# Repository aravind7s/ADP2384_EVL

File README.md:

# ADP2384_EVL

Hardware design files for a **12 V → 3.3 V @ 4 A** DC-DC buck converter based on the **Analog Devices ADP2384** designed using KiCad.

---

## 🧭 Overview

This project contains the complete design package — schematic, layout, and simulation files — for a compact, high-efficiency step-down converter using the ADP2384 synchronous buck regulator.  

---

## ⚙️ Board Specifications

| Parameter | Specification |
|------------|---------------|
| Input Voltage | 12 V |
| Output Voltage | 3.3 V |
| Output Current | Up to 4 A |
| Regulator IC | ADP2384 |
| Board Dimensions | 35 mm × 40 mm |
| PCB Layers | 2 layers |
| Assembly | Single-sided |

---

*3D render of the ADP2384_EVL board (35 × 40 mm)*

*Front Side*

*Back Side*

---

## 📂 Repository Structure
/

├── Board_Files/ # Schematics, BOM, PCB layout and Gerbers

├── Simulation_Files/ # LTspice file

├── TechRef/ # Datasheets and application notes

├── images/ # Renders, photos, documentation images

├── LICENSE

└── README.md

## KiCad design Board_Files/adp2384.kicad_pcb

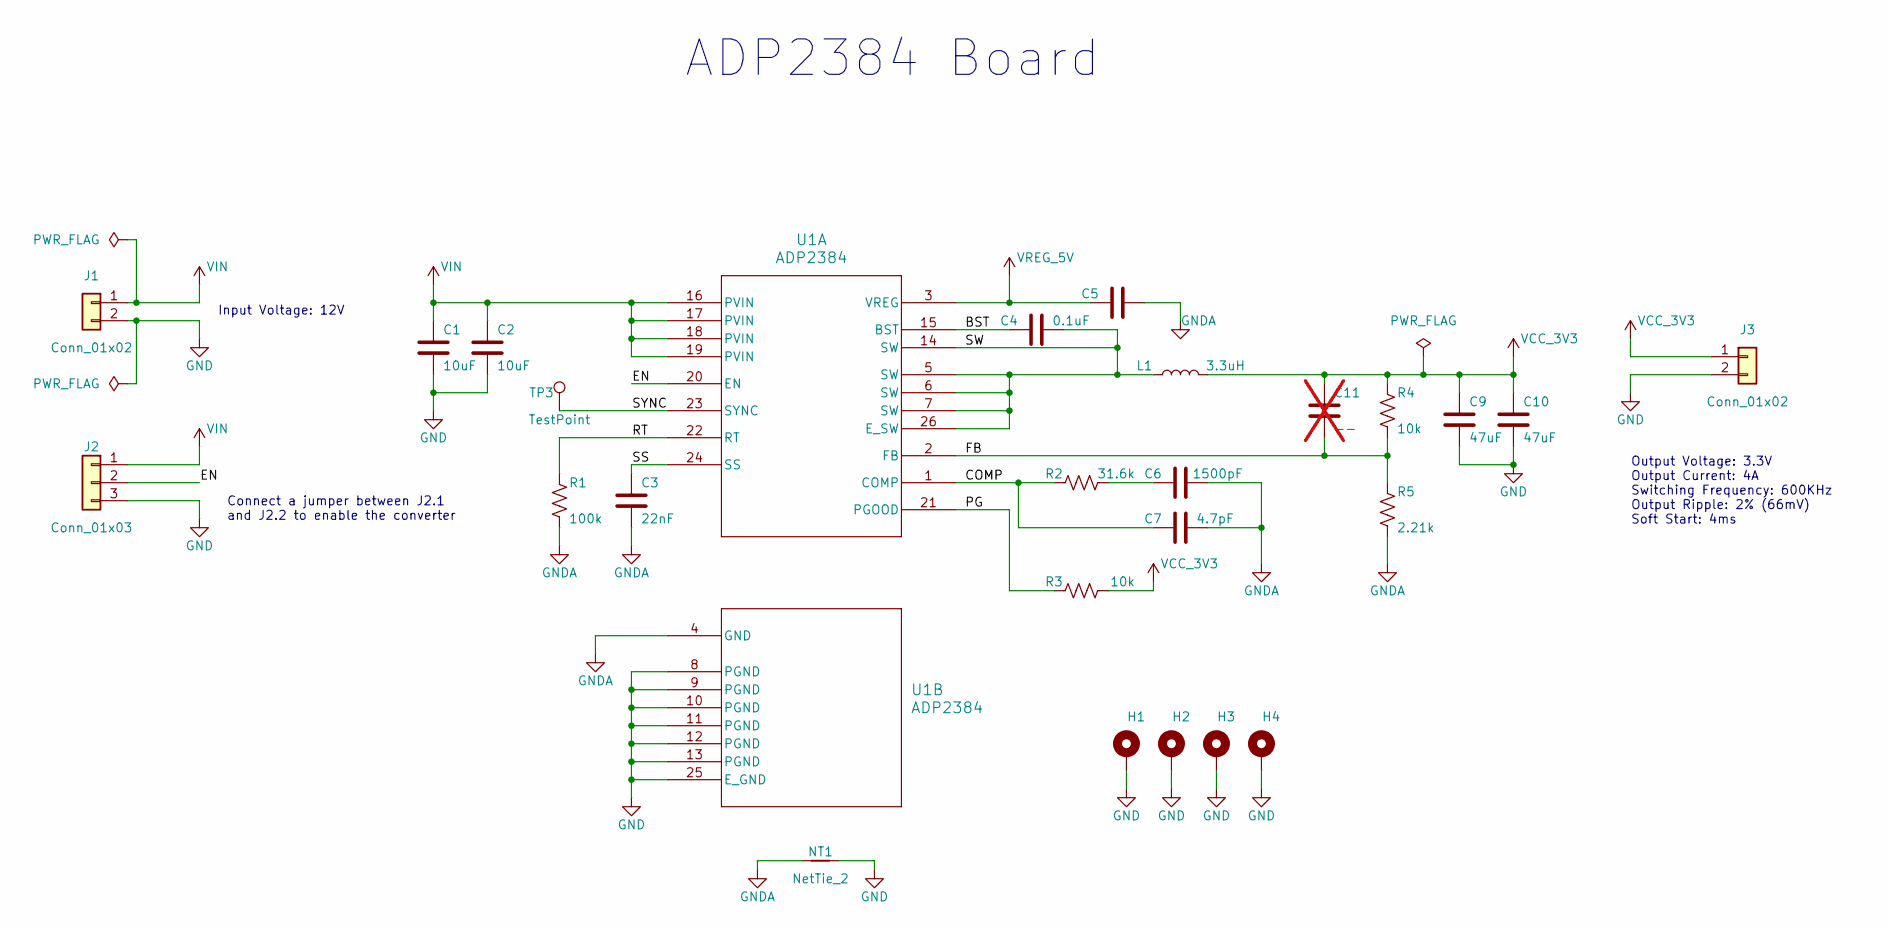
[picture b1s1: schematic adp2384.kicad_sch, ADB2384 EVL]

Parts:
C1, C2: 10uF; C_1206_3216Metric; Mfg Part No CL31B106KAHNNNE
C3: 22nF; C_0603_1608Metric; Mfg Part No GCM188R72A223KA37J
C4: 0.1uF; C_0603_1608Metric; Mfg Part No CC0603KRX7R9BB104
C5: 1uF; C_0603_1608Metric; Mfg Part No CL10B105KO8NNNC
C6: 1500pF; C_0603_1608Metric; Mfg Part No GRM1885C1H152JA01D
C7: 4.7pF; C_0603_1608Metric; Mfg Part No CC0603CPNPO9BN4R7
C9, C10: 47uF; C_1206_3216Metric; Mfg Part No GRM31CR61A476ME15L
C11: --; C_0603_1608Metric; Mfg Part No NA; not fitted
H1, H2, H3, H4: MountingHole_Pad; MountingHole_3.2mm_M3_DIN965_Pad_TopBottom; Mfg Part No NA
J1, J3: Conn_01x02; PinHeader_1x02_P2.54mm_Vertical; Mfg Part No PH1-02-UA
J2: Conn_01x03; PinHeader_1x03_P2.54mm_Vertical; Mfg Part No PH1-03-UA
L1: 3.3uH; IND_IHLP-4040DZ_VIS; Mfg Part No IHLP4040DZER3R3M01
NT1: NetTie_2; NetTie-2_THT_Pad0.3mm; Mfg Part No NA
R1: 100k; R_0603_1608Metric; Mfg Part No CRCW0603100KFKEA
R2: 31.6k; R_0603_1608Metric; Mfg Part No CRCW060331K6FKEA
R3, R4: 10k; R_0603_1608Metric; Mfg Part No CRCW060310K0FKEA
R5: 2.21k; R_0603_1608Metric; Mfg Part No CRCW06032K21FKEA
TP3: TestPoint; TestPoint_Pad_D1.0mm; Mfg Part No NA
U1: ADP2384; CP_24_12_ADI; Mfg Part No ADP2384ACPZN-R7

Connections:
/BST: C4.2, U1.15 (BST)
/COMP: C7.2, R2.1, U1.1 (COMP)
/EN: J2.2, U1.20 (EN)
/FB: C11.1, R4.2, R5.1, U1.2 (FB)
/PG: R3.1, U1.21 (PGOOD)
/RT: R1.1, U1.22 (RT)
/SS: C3.2, U1.24 (SS)
/SW: C4.1, L1.1, U1.5 (SW), U1.6 (SW), U1.7 (SW), U1.14 (SW), U1.26 (E_SW)
/SYNC: TP3.1, U1.23 (SYNC)
GND: C1.1, C2.1, C9.1, C10.1, H1.1, H2.1, H3.1, H4.1, J1.2, J2.3, J3.2, NT1.2, U1.8 (PGND), U1.9 (PGND), U1.10 (PGND), U1.11 (PGND), U1.12 (PGND), U1.13 (PGND), U1.25 (E_GND)
GNDA: C3.1, C5.1, C6.1, C7.1, NT1.1, R1.2, R5.2, U1.4 (GND)
unnamed: C6.2, R2.2
VCC_3V3: C9.2, C10.2, C11.2, J3.1, L1.2, R3.2, R4.1
VIN: C1.2, C2.2, J1.1, J2.1, U1.16 (PVIN), U1.17 (PVIN), U1.18 (PVIN), U1.19 (PVIN)
VREG_5V: C5.2, U1.3 (VREG)

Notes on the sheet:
ADP2384 Board
Output Voltage: 3.3V Output Current: 4A Switching Frequency: 600KHz Output Ripple: 2% (66mV) Soft Start: 4ms
Connect a jumper between J2.1 and J2.2 to enable the converter
Input Voltage: 12V

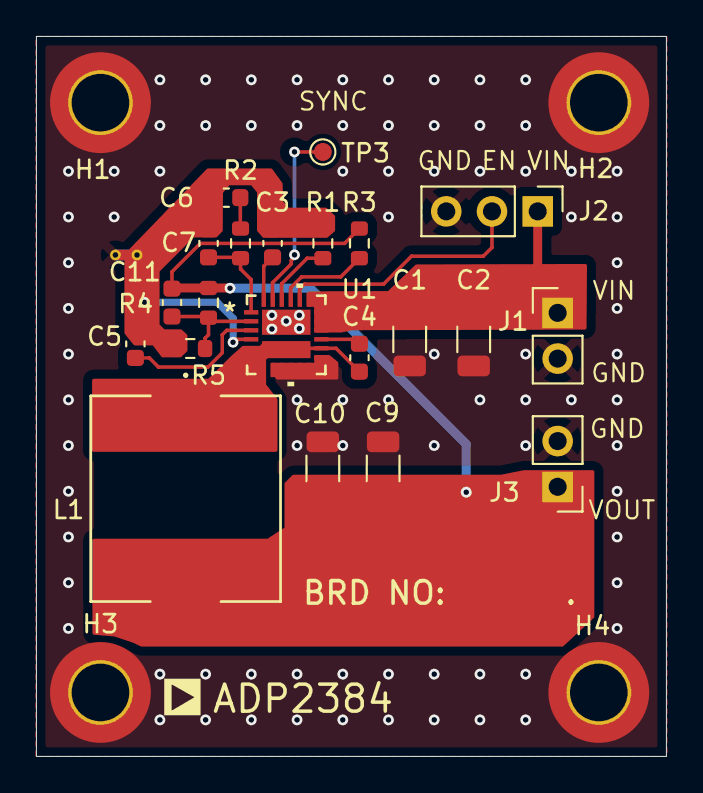
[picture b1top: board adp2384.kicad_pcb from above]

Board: 2 copper layers, 35.0 x 40.0 mm, 26 parts (0 on the bottom side), 15 nets.

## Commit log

2025-10-20 First Release
    Schematics, LTSpice Simulation, Layout, and Gerber Files uploaded.
2025-10-20 Update A1 Release files
    1. Added design information in Schematics.
    2. BOM generated.
    3. Updated the library path to align with the current folder structure.
    4. Added 3D board file images.
    5. Updated README.
2025-10-20 Update README.md
    Updated README file
2025-10-20 Updated BOM
    Removed the DNP components
